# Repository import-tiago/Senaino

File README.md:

# Senaino

Senaino is an educational microcontroller board inspired by the Arduino UNO and adapted for technical training at SENAI. It was designed to help students practice soldering, electronics, bootloader recording and embedded programming with components that are easy to source in Brazil.

## Overview

The goal was not only to make an Arduino-compatible board, but to create a reproducible hardware kit that could be fabricated, assembled and tested by students in a classroom or lab environment.

The work included schematic design, PCB layout, component selection, production files, assembly references, documentation and validation of the mounted board.

## Highlights

- Arduino UNO-inspired board based on the ATmega328P-PU.
- Two documented USB-to-serial variants: FT232RL and CH340G.
- Through-hole component strategy for beginner-friendly soldering practice.
- 16 MHz ATmega328P clock and Arduino-style headers.
- Open hardware files for Eagle, Gerber fabrication, schematic export and BOM.
- Dedicated assembly, testing, driver and bootloader documentation.

## Repository Map

```text
assets/
  images/          Project photos and workshop/gallery images.
  reference/       Board overlays and visual references for assembly.

docs/
  ft232/           FT232 assembly, BOM, production and testing notes.
  ch340/           CH340 assembly, BOM, production and testing notes.
  citation.md
  design-decisions.md
  drivers.md
  licensing.md
  variants.md

hardware/
  bom/             Spreadsheet and CSV bill of materials.
  eagle/           Eagle schematic and board files by variant.
  exports/         Schematic image/PDF exports.
  gerbers/         Fabrication files by variant.
```

## Documentation

- [Bootloader notes](docs/bootloader.md)
- [Citation and DOI guide](docs/citation.md)
- [Design decisions](docs/design-decisions.md)
- [Driver notes](docs/drivers.md)
- [License notes](docs/licensing.md)
- [Board variants](docs/variants.md)

| Variant | Assembly | Board overlay | BOM | Production | Testing |
|---|---|---|---|---|---|
| FT232 | [Guide](docs/ft232/assembly-guide.md) | [Overlay](assets/reference/senaino-ft232-components-silkscreen.png) | [BOM](docs/ft232/bill-of-materials.md) | [Files](docs/ft232/production.md) | [Checklist](docs/ft232/testing.md) |
| CH340 | [Guide](docs/ch340/assembly-guide.md) | [Overlay](assets/reference/senaino-ch340-components-silkscreen.png) | [BOM](docs/ch340/bill-of-materials.md) | [Files](docs/ch340/production.md) | [Checklist](docs/ch340/testing.md) |

## Hardware Files

| Variant | Eagle files | Schematic PDF | Gerbers | BOM |
|---|---|---|---|---|
| FT232 | [hardware/eagle/ft232-v1.0](hardware/eagle/ft232-v1.0) | [PDF](hardware/exports/senaino-ft232-schematic.pdf) | [Gerbers](hardware/gerbers/ft232-v1.0) | [CSV](hardware/bom/senaino-ft232-bom.csv) |
| CH340 | [hardware/eagle/ch340-v1.0](hardware/eagle/ch340-v1.0) | [PDF](hardware/exports/senaino-ch340-schematic.pdf) | [Gerbers](hardware/gerbers/ch340-v1.0) | [CSV](hardware/bom/senaino-ch340-bom.csv) |

## Board Variants

The repository documents two board variants in the `main` branch.

| Variant | USB-serial IC | Main advantage | Recommended use |
|---|---|---|---|
| FT232 | FT232RL | Traditional and widely documented | Original classroom version |
| CH340 | CH340G | Lower cost and avoids FT232 sourcing risk | Cost-sensitive or supply-risk-aware production |

The CH340 alternative exists because FT232RL sourcing can be risky. ZeptoBars documented real and fake FT232RL dies and described counterfeit/compatible chips that could behave differently with FTDI drivers: [FTDI FT232RL: real vs fake](https://zeptobars.com/en/read/FTDI-FT232RL-real-vs-fake-supereal).

## Gallery

| | | |
|---|---|---|
|  |  |  |
|  |  |  |
|  |  |  |

## Credits

Senaino was designed by Tiago Silva for educational use with [SENAI](https://www.sp.senai.br/) students. The board is inspired by the Arduino UNO reference design and keeps the educational spirit of open hardware.

## Citation

Citation metadata is available in [CITATION.cff](CITATION.cff).

## Contributing

See [CONTRIBUTING.md](CONTRIBUTING.md).

## License

The hardware design files are licensed under CERN-OHL-S-2.0. Documentation, images and educational material are licensed under CC BY-SA 4.0. See [LICENSE](LICENSE) and [docs/licensing.md](docs/licensing.md).

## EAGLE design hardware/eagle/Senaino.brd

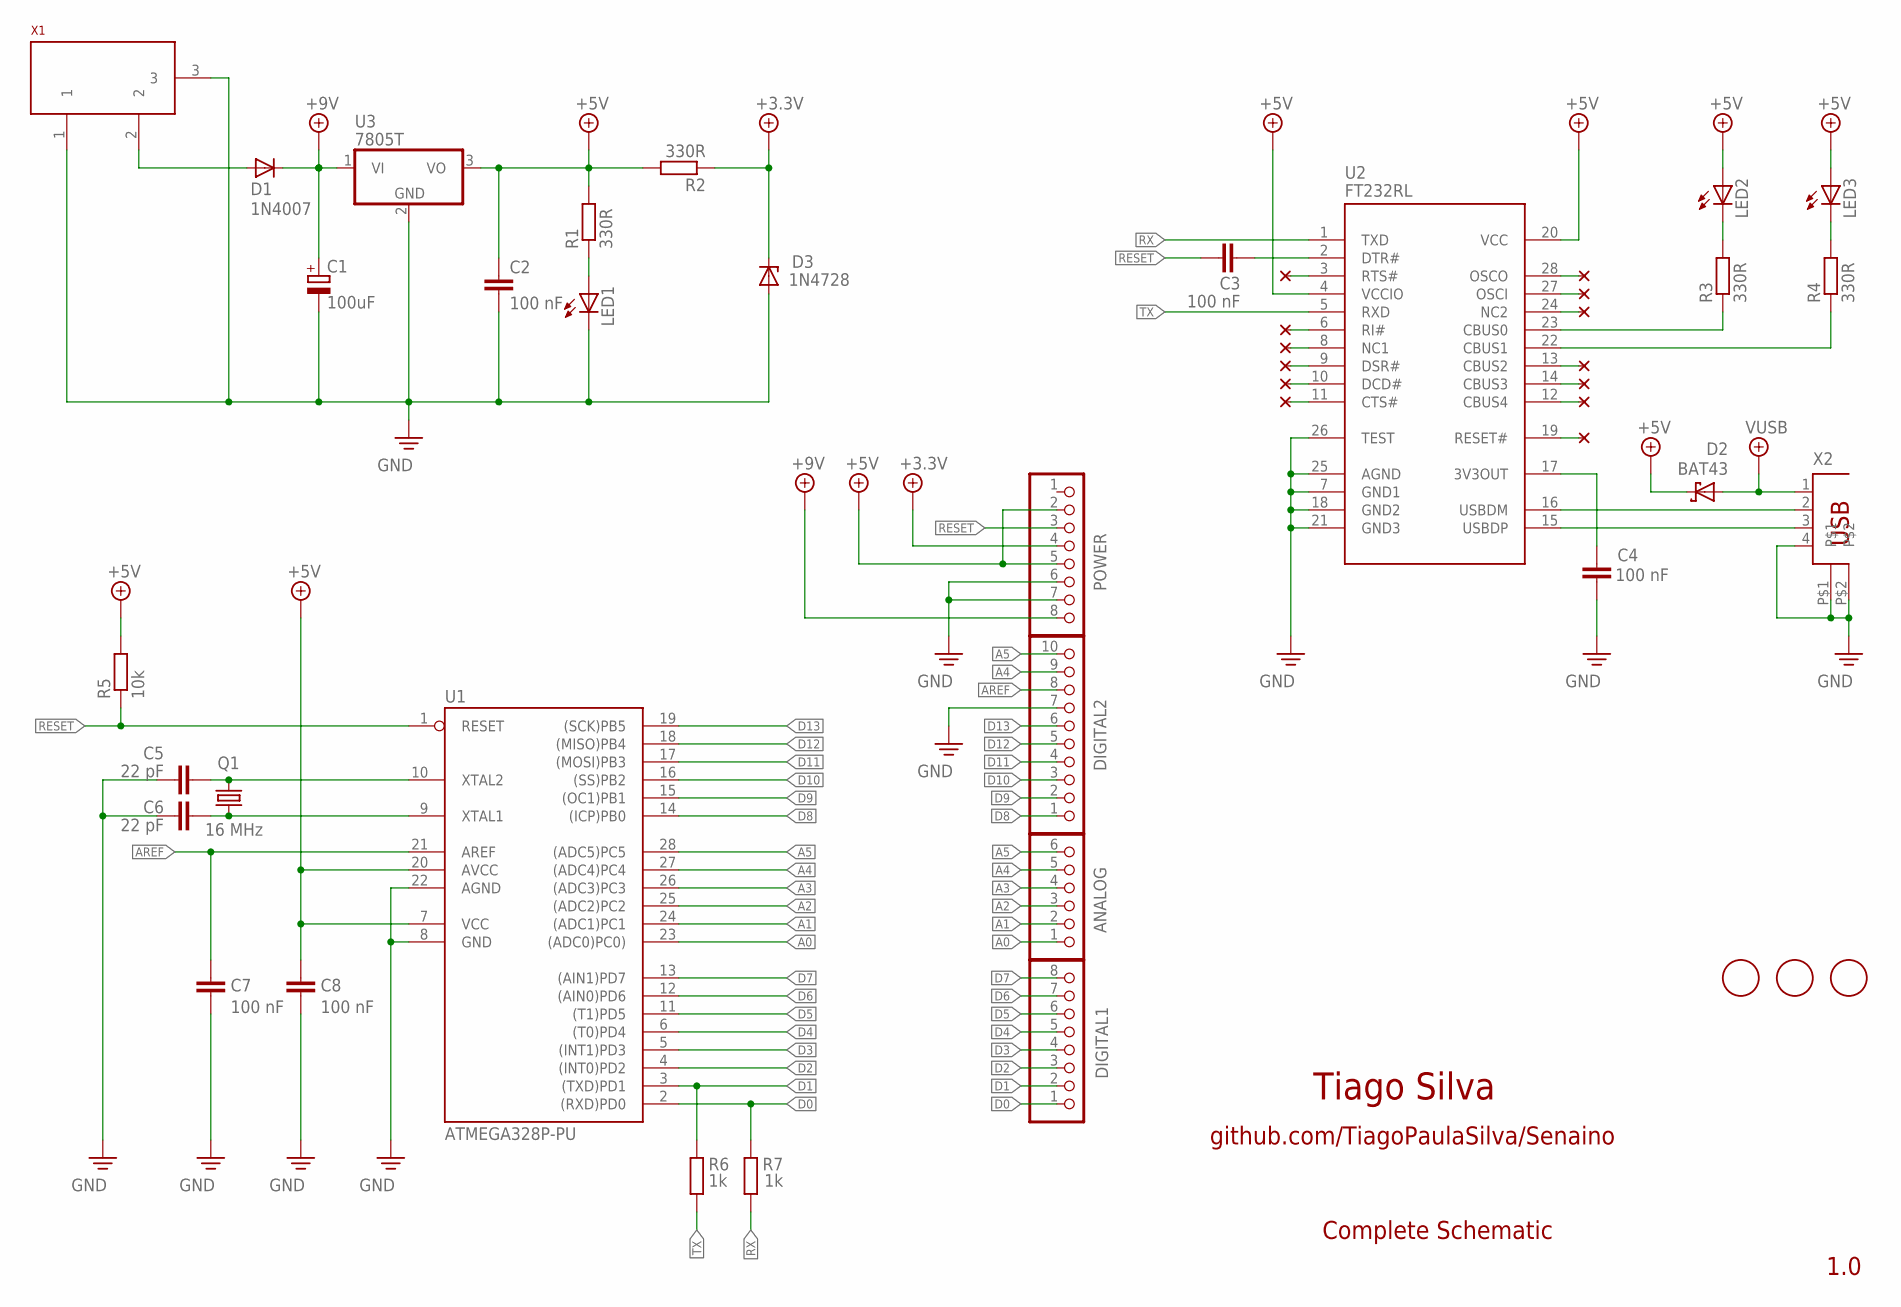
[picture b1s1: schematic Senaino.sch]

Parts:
ANALOG: PINHD-1X6; 1X06
C1: 100uF; E2-5
C2, C3, C4, C7, C8: 100 nF; C025-024X044
C5, C6: 22 pF; C025-024X044
D1: 1N4007; DO35-7
D2: BAT43; DIODE_DO35-7
D3: 1N4728; DO41Z10
DIGITAL1: PINHD-1X8; 1X08
DIGITAL2: PINHD-1X10_ARD; 1X10
FD1, FD2, FD3: FIDUCIALMOUNT; FIDUCIA-MOUNT
LED1, LED2, LED3: LED3MM
POWER: PINHD-1X8; 1X08
Q1: 16 MHz; HC49/S
R1, R2, R3, R4: 330R; 0204/7
R5: 10k; 0204/7
R6, R7: 1k; 0204/7
U1: ATMEGA328P-PU; DIL28-3
U2: FT232RL; SSOP28
U3: 7805T; TO220H
X1: POWERSUPPLY_DC21MMX; POWERSUPPLY_DC-21MM
X2: PN61729

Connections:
+3.3V: D3.C, POWER.4, R2.1
+5V: C2.1, C8.1, D2.C (A), LED2.A, LED3.A, POWER.2, POWER.5, R1.2, R2.2, R5.2, U1.7 (VCC), U1.20 (AVCC), U2.4 (VCCIO), U2.20 (VCC), U3.3 (VO)
+9V: C1.+, D1.C, POWER.8, U3.1 (VI)
A0: ANALOG.1, U1.23 ((ADC0)PC0))
A1: ANALOG.2, U1.24 ((ADC1)PC1)
A2: ANALOG.3, U1.25 ((ADC2)PC2)
A3: ANALOG.4, U1.26 ((ADC3)PC3)
A4: ANALOG.5, DIGITAL2.9, U1.27 ((ADC4)PC4)
A5: ANALOG.6, DIGITAL2.10, U1.28 ((ADC5)PC5)
AREF: C7.1, DIGITAL2.8, U1.21 (AREF)
D0: DIGITAL1.1, R7.2, U1.2 ((RXD)PD0)
D1: DIGITAL1.2, R6.2, U1.3 ((TXD)PD1)
D2: DIGITAL1.3, U1.4 ((INT0)PD2)
D3: DIGITAL1.4, U1.5 ((INT1)PD3)
D4: DIGITAL1.5, U1.6 ((T0)PD4)
D5: DIGITAL1.6, U1.11 ((T1)PD5)
D6: DIGITAL1.7, U1.12 ((AIN0)PD6)
D7: DIGITAL1.8, U1.13 ((AIN1)PD7)
D8: DIGITAL2.1, U1.14 ((ICP)PB0)
D9: DIGITAL2.2, U1.15 ((OC1)PB1)
D10: DIGITAL2.3, U1.16 ((SS)PB2)
D11: DIGITAL2.4, U1.17 ((MOSI)PB3)
D12: DIGITAL2.5, U1.18 ((MISO)PB4)
D13: DIGITAL2.6, U1.19 ((SCK)PB5)
GND: C1.-, C2.2, C4.1, C5.1, C6.1, C7.2, C8.2, D3.A, DIGITAL2.7, LED1.K (C), POWER.6, POWER.7, U1.8 (GND), U1.22 (AGND), U2.7 (GND1), U2.18 (GND2), U2.21 (GND3), U2.25 (AGND), U2.26 (TEST), U3.2 (GND), X1.1, X1.3, X2.4, X2.P$1, X2.P$2
unnamed: D1.A, X1.2
unnamed: U2.16 (USBDM), X2.2
unnamed: C3.2, U2.2 (DTR#)
unnamed: R3.1, U2.23 (CBUS0)
unnamed: U2.15 (USBDP), X2.3
unnamed: LED2.K (C), R3.2
unnamed: LED3.K (C), R4.2
unnamed: R4.1, U2.22 (CBUS1)
unnamed: C4.2, U2.17 (3V3OUT)
unnamed: C5.2, Q1.2, U1.10 (XTAL2)
unnamed: C6.2, Q1.1, U1.9 (XTAL1)
unnamed: LED1.A, R1.1
RESET: C3.1, POWER.3, R5.1, U1.1 (RESET)
RX: R7.1, U2.1 (TXD)
TX: R6.1, U2.5 (RXD)
VUSB: D2.A (C), X2.1

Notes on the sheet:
Tiago Silva
github.com/TiagoPaulaSilva/Senaino
1.0
Complete Schematic

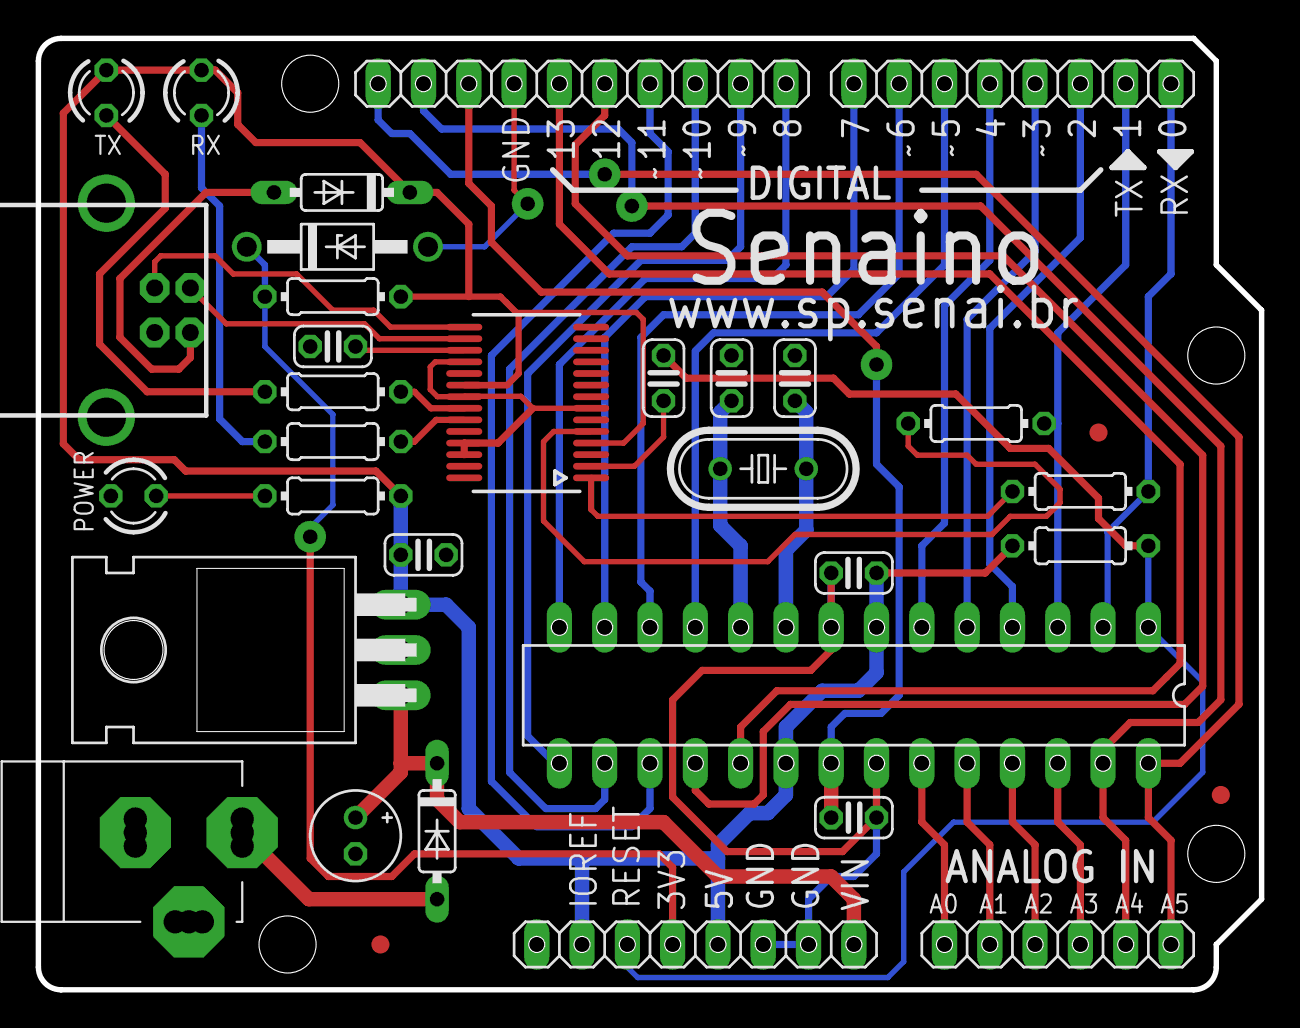
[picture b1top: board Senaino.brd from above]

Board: 2 copper layers, 68.6 x 53.3 mm, 34 parts (0 on the bottom side), 41 nets.

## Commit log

2017-04-27 Add files via upload
    100% functional design.
2017-06-21 Update README.md
    Inserting Illustrative Image
2017-06-24 Update README.md
    Entering license Information.
2017-06-24 Update README.md
    Change the language in the text about the type of project license (PT-BR to EN-US).
2017-08-28 Add files via upload
    bill of materials
2017-11-14 Add files via upload
    add pdf sch file
2018-07-18 FTDI Driver Upoload
2018-07-18 Update README.md
    Recommended FTDI Driver
2019-06-19 USB/Serial Converter Chip Change
    - The FT232 USB/Serial converter changed by CH340.
    - The reason for this is to create a second alternative to FT232 converter. This is not always available in large quantities in the Brazilian market.
    - In addition, CH340 encapsulation is easier to solder on the board.
2019-06-19 Files organized by folders
    - Nothing has changed in the project.
    - Only improved the organization of the files.
2019-06-20 Changes to CH340 performed
    - Schematic OK.
    - Layout OK.
    - BOM OK.
2019-07-22 .gitattributes file added
2019-07-22 Frame schematic updated
2019-07-22 Readme updated
2019-11-09 pin 1 from CH340 added to GND & R3/R4 changed to 1k
2019-11-09 Schematic 2.1 updated
2019-11-09 BOM updated with 2.1 schematic
2019-11-09 Mounted board photo updated with 2.1 schematic
2019-11-09 CH340 driver added
2019-11-09 New gerber files generated from 2.1 schematic
2019-11-09 Mounted Board Photo.jpeg resized
2019-11-09 Mounted Board Photo updated
2019-11-09 Minor improvements
2019-11-16 Add schematic as a image
2019-11-18 All files added to a .rar file
2020-01-16 SENAI students working on Senaino photos
2023-07-21 usernames in URLs updated
2026-06-17 Reorganize repository for portfolio presentation
2026-06-17 Update default branch references
2026-06-17 Reorganize CH340 branch documentation
2026-06-17 Prepare FT232 release citation metadata
2026-06-17 Prepare CH340 release citation metadata
2026-06-17 Refine README overview wording
2026-06-17 Refine CH340 README overview wording
2026-06-17 Consolidate CH340 variant into main
2026-06-17 Document board overlays for release
2026-06-17 Use absolute overlay links in release notes
2026-06-17 Update README by removing badges
    Removed variant and status badges from README.
2026-06-19 Fix citation instructions in README.md

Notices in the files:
README.md:
License: CERN-OHL-S-2.0 + CC-BY-SA-4.0
